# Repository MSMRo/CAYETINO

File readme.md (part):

# ⚡ Proyecto CAYETINO

Dispositivo generador de biopotenciales y señales sintéticas (EKG, EMG, EEG, RSP, PPG y ondas básicas) para entrenamiento y docencia de estudiantes de Ingeniería Biomédica.

El sistema se compone de dos módulos interconectados:
1. **Frontend / Interfaz de Control (Streamlit)**: Aplicación interactiva en Python que permite diseñar ondas básicas, sintetizar señales fisiológicas avanzadas con la librería **NeuroKit2**, inyectar fuentes de ruido clínico (interferencia electromagnética a 60 Hz, ruido térmico blanco y artefactos de movimiento), transferir los archivos vía Serial y gestionar la reproducción del hardware.
2. **Firmware de Adquisición y Emisión DAC (ESP32 en Arduino)**: Programa embebido que recibe los datos por comunicación serial por bloques con ACK, los almacena en el sistema de archivos no volátil **LittleFS**, y los reproduce en bucle continuo a través de su convertidor digital-analógico interno de 8 bits (**GPIO 25 / GPIO 26**) mediante un temporizador por hardware de 64 bits (`esp_timer`).

---

## 📁 Estructura del Repositorio

```
CAYETINO/
├── app_pyqt6/                        # Interfaz nativa de escritorio en PyQt6
│   ├── main.py                      # Punto de entrada de la aplicación de escritorio
│   ├── main_window.py               # Ventana principal e integración de pestañas
│   ├── sidebar.py                   # Enlace serial, simulación y control DAC
│   ├── tab_basic.py                 # Modo básico: formas de onda periódicas
│   ├── tab_advanced.py              # Modo avanzado: biopotenciales y NeuroKit2
│   ├── tab_manager.py               # Explorador de archivos LittleFS y reproducción DAC
│   ├── tab_guide.py                 # Guía de hardware, circuito atenuador y protocolo
│   ├── styles.py                    # Hoja de estilos moderna inspirada en Streamlit
│   ├── workers.py                   # Subprocesos QThread asíncronos para Serial
│   ├── signal_generator.py          # Motor de síntesis fisiológica y ruido
│   └── serial_comm.py               # Driver de comunicación UART y LittleFS
├── app_streamlit/                    # Interfaz web de usuario y control (Streamlit)
│   ├── app.py                       # Aplicación principal de Streamlit
│   ├── signal_generator.py          # Síntesis matemática, NeuroKit2 y ruido
│   ├── serial_comm.py               # Driver de comunicación serial y LittleFS
│   └── requirements.txt             # Dependencias en Python
├── dist/
│   └── Cayetino_ESP32/              # Carpeta de distribución del ejecutable Windows
│       └── Cayetino_ESP32.exe       # Ejecutable nativo (.exe) para PC
├── firmware_esp32/
│   └── cayetino_esp32/
│       ├── cayetino_esp32.ino       # Código Arduino/C++ para ESP32
│       └── README.md                # Guía de compilación y flasheo
├── CIRCUITO_KICAD/                  # Archivos de hardware y PCB
├── run_cayetino_exe.bat             # Lanzador directo del ejecutable .exe compilado
├── run_app_pyqt.bat                 # Lanzador de la app PyQt6 en Python
├── run_app.bat                      # Lanzador de la app Streamlit
└── README.md                        # Documentación general
```

---

## 🚀 Inicio Rápido

### 1. Ejecutar el Ejecutable .EXE (Instalable/Portable en PC)
No requiere tener Python instalado:
- Haz doble clic en **`run_cayetino_exe.bat`** o abre directamente:
  `dist\Cayetino_ESP32\Cayetino_ESP32.exe`

### 2. Ejecutar la versión PyQt6 en Python
```powershell
.\run_app_pyqt.bat
```
O directamente con Python:
```powershell
python app_pyqt6/main.py
```

### 3. Ejecución de la Interfaz Streamlit
Haz doble clic en `run_app.bat` o ejecuta:
```powershell
python -m streamlit run app_streamlit/app.py
```

---

## 🌟 Funcionalidades Detalladas

### 1. 📊 Modo Básico
- **Formas de onda disponibles**:
  - Senoidal
  - Triángulo
  - Cuadrada (con ciclo de trabajo ajustable)
  - Diente de sierra
  - Diente de sierra invertida
- **Parámetros configurables**:
  - Frecuencia de la señal ($f$ en Hz)
  - Frecuencia de muestreo ($F_s$ en Hz)
  - Duración de la ventana temporal ($T$ en segundos)
  - Amplitud y nivel de offset DC
- **Previsualización en tiempo real**: Visualización con **Plotly** de la forma de onda continua, la tensión de salida analógica ($0.0 - 3.3\text{ V}$) y el código digital cuantizado DAC ($0 - 255$).
- **Exportación**: Envío directo a la memoria flash LittleFS del ESP32 con selector de formato (`.csv`, `.txt`, `.dat`).

### 2. 🧬 Modo Avanzado (NeuroKit2 & Simulación Fisiológica)
- **Señales biomédicas sintéticas**:
  - **EKG / ECG**: Modelo dinámico de McSharry (*ecgsyn*) o modelo estándar, con ritmo cardíaco ajustable (BPM).
  - **EMG**: Electromiografía con ráfagas de activación y duración de contracción configurables.
  - **EEG**: Ondas electroencefalográficas con mezcla de ritmos fisiológicos (Alpha, Beta, Theta y componente estocástico 1/f).
  - **RSP**: Dinámica respiratoria sinusoidal con variabilidad.
  - **PPG**: Pulso arterial y fotopletismografía.
- **Módulo de Contaminación de Señales (Inyección de Ruido)**:
  - ⚡ **Interferencia de Red Eléctrica**: Onda senoidal armónica (60 Hz por defecto en Perú/América o 50 Hz) con amplitud graduable.
  - 🌫️ **Ruido Blanco Térmico**: Distribución Gaussiana $\mathcal{N}(0, \sigma^2)$ para modelar ruido de electrodo y circuitería analógica.
  - 📍 **Ruido Impulsional**: Artefactos de movimiento y desacople de electrodos (spikes aleatorios bipolares).
- **Análisis en Frecuencia (FFT)**: Espectro de potencia en tiempo real para verificar la presencia de armónicos contaminantes (pico a 60 Hz).

### 3. 💾 Gestor de Archivos en LittleFS y Control del DAC
- **Explorador Flash**: Muestra un cuadro/tarjeta con todos los archivos guardados en la memoria del ESP32, indicando:
  - Nombre del archivo
  - Frecuencia de muestreo original ($F_s$)
  - Cantidad total de muestras
  - Duración de la ventana en segundos
  - Tamaño ocupado en memoria Flash
- **Controles de Reproducción**:
  - ▶ **Reproducir (PLAY)**: El ESP32 carga la señal en memoria RAM y comienza la emisión analógica ininterrumpida en bucle por su DAC.
  - ⏹ **Detener (STOP)**: Detiene la emisión analógica y coloca la salida en nivel seguro de reposo ($\sim 1.65\text{ V}$).
  - 🗑 **Eliminar**: Borra el archivo seleccionado del sistema de archivos LittleFS.
  - 🔄 **Actualizar**: Lee el estado actual y archivos de la memoria del ESP32.
---

## 🏛️ Arquitectura del Sistema y Diagramas Técnicos (Mermaid)

Para comprender en profundidad el funcionamiento integral de la plataforma Cayetino (desde el diseño en el frontend de escritorio hasta la síntesis en tiempo real por interrupción en el microcontrolador), se detallan a continuación los diagramas arquitectónicos del proyecto:

---

### 1. 📐 Modelo C4 de Arquitectura

El modelo C4 permite descomponer la arquitectura en diferentes niveles de abstracción jerárquica:

#### Nivel 1: Diagrama de Contexto del Sistema (System Context)
Muestra cómo interactúa el usuario (estudiante o investigador biomédico) con la plataforma Cayetino y los equipos de instrumentación clínica externos.

```mermaid
flowchart TB
  subgraph Contexto ["C4 - Nivel 1: Contexto del Sistema CAYETINO"]
    User["👨‍🔬 Usuario Biomédico<br>[Estudiante / Investigador / Docente]<br>Diseña ondas, inyecta ruido clínico y controla reproducción"]
    
    CayetinoSystem["⚡ <b>Sistema CAYETINO</b><br>[Generador de Biopotenciales y Ondas Sintéticas]<br>Plataforma de software y hardware embebido basada en ESP32"]
    
    BioAmp["🩺 Amplificador de Biopotenciales<br>[AD620 / INA128 / ADS1299]<br>Captación de señales en rango de microvoltios/milivoltios"]
    
    Oscilloscope["📈 Instrumental de Diagnóstico<br>[Osciloscopio / DAQ / Raspberry Pi Pico ADC]<br>Medición y análisis directo en dominio temporal y espectral"]
    
    PC_Host["💻 Computadora Personal Windows<br>[Host PC]<br>Alimentación USB y canal UART bidireccional (115200 bps)"]

    User -->|"Configura parámetros y gestiona memoria Flash"| CayetinoSystem
    CayetinoSystem -->|"Emite señal atenuada segura (0.1 a 3.3 mV)"| BioAmp
    CayetinoSystem -->|"Emite señal DAC pura (0.0 a 3.3 V)"| Oscilloscope
    PC_Host <-->|"Enlace USB-UART Serial (CP210x)"| CayetinoSystem
  end
```

#### Nivel 2: Diagrama de Contenedores (Containers)
Describe las aplicaciones ejecutables, el firmware embebido en el ESP32, el almacenamiento Flash y el circuito atenuador pasivo.

```mermaid
flowchart TB
  subgraph Containers ["C4 - Nivel 2: Diagrama de Contenedores"]
    User["👨‍🔬 Usuario Biomédico"]

    subgraph HostPC ["Computadora Personal (Entorno Windows)"]
      PyQtApp["🖥️ <b>Aplicación de Escritorio PyQt6</b><br>[Python 3.12 / PyQt6 / PyInstaller .EXE]<br>Interfaz gráfica nativa de alto rendimiento con pyqtgraph y workers QThread"]
      StreamlitApp["🌐 <b>Aplicación Web Streamlit</b><br>[Python / Streamlit / Plotly]<br>Panel web interactivo accesible vía navegador local"]
    end

    subgraph EmbeddedESP32 ["Módulo Embebido ESP32 (Hardware Microcontrolador)"]
      FirmwareCore["⚙️ <b>Firmware C++ Cayetino</b><br>[Arduino Core / FreeRTOS / UART Driver]<br>Intérprete de comandos seriales, parser de chunks y despachador"]
      TimerEngine["⏱️ <b>Temporizador de Hardware</b><br>[esp_timer 64-bit]<br>Genera interrupciones periódicas a frecuencia exacta Fs"]
      FlashStorage[("💾 <b>Sistema de Archivos Flash</b><br>[LittleFS non-volatile]<br>Almacena archivos .csv, .txt y .dat de señales")]
      DACModule["⚡ <b>Convertidor DAC 8-bit</b><br>[Hardware DAC interno ESP32]<br>Emisión analógica por GPIO 25 o GPIO 26"]
    end

    subgraph CircuitPCB ["Placa de Acondicionamiento (Circuito KiCad)"]
      Attenuator["🎛️ <b>Divisor Atenuador Pasivo 1000:1</b><br>[R1 = 10 kΩ, R2 = 10 Ω]<br>Reduce la tensión de 3.3 V a niveles fisiológicos seguros"]
    end

    BioAmpExternal["🩺 Amplificador / Electrocardiógrafo Externo"]

    User -->|"Control interactivo nativo"| PyQtApp
    User -->|"Control web"| StreamlitApp
    PyQtApp <-->|"Comandos de texto y datos UART (115200 bps)"| FirmwareCore
    StreamlitApp <-->|"Comandos de texto y datos UART (115200 bps)"| FirmwareCore

    FirmwareCore <-->|"Lectura y escritura por bloques"| FlashStorage
    FirmwareCore -->|"Carga buffer a RAM y configura periodo"| TimerEngine
    TimerEngine -->|"Interrupción periódica dacWrite()"| DACModule
    DACModule -->|"Tensión analógica (0.0 V - 3.3 V)"| Attenuator
    Attenuator -->|"Tensión biomédica (0.1 mV - 3.3 mV)"| BioAmpExternal
  end
```

#### Nivel 3: Diagrama de Componentes (Components)
Detalla los módulos internos del frontend PyQt6 y las rutinas del firmware Arduino/C++.

```mermaid
flowchart TB
  subgraph ComponentsDiagram ["C4 - Nivel 3: Componentes de Software y Firmware"]
    subgraph FrontendPyQt6 ["Contenedor: Aplicación de Escritorio (app_pyqt6)"]
      MainWindow["<b>MainWindow</b><br>Ventana principal, control de pestañas y notificaciones flotantes"]
      Sidebar["<b>SidebarWidget</b><br>Gestión de puertos COM, modo simulación, selección DAC y formateo"]
      TabBasic["<b>TabBasicWave</b><br>Generador de ondas sintéticas, previsualización dual y guardado"]
      TabAdv["<b>TabAdvancedBio</b><br>Modelado NeuroKit2, inyector de 3 ruidos clínicos y FFT"]
      TabMgr["<b>TabManager</b><br>Tabla LittleFS, reproductor PLAY/STOP y prueba senoidal 5Hz"]
      TabGde["<b>TabGuide</b><br>Documentación interactiva y tabla del protocolo serial"]
      SignalGen["<b>signal_generator.py</b><br>Motor numérico: scipy.signal, neurokit2 y cuantización 8-bit"]
      Workers["<b>workers.py (QThreads)</b><br>ConnectWorker, SaveSignalWorker, PlayWorker, ListWorker, etc."]
      SerialDriver["<b>serial_comm.py (CayetinoSerial)</b><br>Controlador de comunicación física pyserial y virtual"]
    end

    subgraph FirmwareESP32 ["Contenedor: Firmware ESP32 (cayetino_esp32.ino)"]
      CmdParser["<b>Command Parser</b><br>Lectura de líneas UART, extracción de comandos y argumentos"]
      FsManager["<b>LittleFS File Manager</b><br>Lectura de encabezados, escritura incremental y borrado"]
      DacController["<b>Playback Controller</b><br>Carga de muestras a RAM estática y gestión de estados"]
      TimerService["<b>esp_timer Service</b><br>Configuración de alarma de microsegundos"]
      DacOutput["<b>DAC Hardware Output</b><br>Escritura analógica directa en registro DAC"]
    end

    MainWindow --> Sidebar
    MainWindow --> TabBasic
    MainWindow --> TabAdv
    MainWindow --> TabMgr
    MainWindow --> TabGde

    TabBasic --> SignalGen
    TabAdv --> SignalGen

    Sidebar --> Workers
    TabBasic --> Workers
    TabAdv --> Workers
    TabMgr --> Workers

    Workers --> SerialDriver
    SerialDriver <-->|"Línea Serial UART (TX/RX)"| CmdParser

    CmdParser --> FsManager
    CmdParser --> DacController
    DacController --> FsManager
    DacController --> TimerService
    TimerService --> DacOutput
  end
```

---

### 2. 🔄 Diagrama de Secuencia (Protocolo UART y Control de Flujo)

Describe el ciclo de vida completo de la comunicación entre la aplicación en la PC y el microcontrolador: handshake, guardado con confirmación por bloques (*stop-and-wait ACK*), reproducción continua por hardware y detención segura.

```mermaid
sequenceDiagram
  autonumber
  actor User as Usuario Biomédico
  participant UI as Interfaz Gráfica (PyQt6)
  participant Worker as QThread Worker (Background)
  participant Driver as CayetinoSerial (Driver PC)
  participant SerialPort as Puerto Serial COM (USB UART)
  participant ESP32 as Firmware ESP32 (Parser)
  participant LittleFS as Memoria Flash (LittleFS)
  participant Timer as esp_timer (Hardware Timer)
  participant DAC as DAC 8-bit (GPIO 25/26)
  participant Circuit as Divisor Atenuador (1000:1)

  %% 1. Handshake
  Note over User, ESP32: 1. Establecimiento de Enlace Serial (Handshake)
  User->>UI: Clic en "Conectar" (COM7, 115200 bps)
  UI->>Worker: Iniciar ConnectWorker(port, 115200)
  Worker->>Driver: connect(port, baudrate)
  Driver->>SerialPort: Abrir conexión COM y limpiar buffers
  Driver->>SerialPort: Enviar "PING\n"
  SerialPort->>ESP32: Recibe "PING"
  ESP32-->>SerialPort: Responde "PONG:CAYETINO_ESP32_OK\n"
  SerialPort-->>Driver: Lectura de respuesta PONG
  Driver-->>Worker: Conexión verificada exitosa (True)
  Worker-->>UI: Emite finished(True)
  UI-->>User: Actualiza estado a "🟢 Conectado"

  %% 2. Guardado con control de flujo
  Note over User, LittleFS: 2. Transmisión y Grabación de Señal en Flash con Flow-Control
  User->>UI: Diseña EKG y pulsa "🚀 Enviar y Guardar"
  UI->>Worker: Iniciar SaveSignalWorker("ekg_5s.csv", 250 Hz, 1250 muestras)
  Worker->>Driver: save_file(filename, fs, dac_values, chunk_size=64)
  Driver->>SerialPort: Enviar "SAVE_START:ekg_5s.csv:250:1250\n"
  SerialPort->>ESP32: Recibe SAVE_START
  ESP32->>LittleFS: LittleFS.open("ekg_5s.csv", "w")
  ESP32-->>SerialPort: Responde "READY_CHUNKS\n"
  SerialPort-->>Driver: Confirma preparación del microcontrolador

  loop Transmisión por bloques de 64 muestras con verificación ACK
    Driver->>SerialPort: Enviar "CHUNK:128,135,142,...\n"
    SerialPort->>ESP32: Escribe bloque en archivo de Flash
    ESP32-->>SerialPort: Responde "ACK_CHUNK\n"
    SerialPort-->>Driver: ACK_CHUNK recibido
    Driver-->>Worker: Notifica avance de progreso (p %)
    Worker-->>UI: Actualiza QProgressBar en tiempo real
  end

  Driver->>SerialPort: Enviar "SAVE_END\n"
  ESP32->>LittleFS: file.close() (Consolida archivo)
  ESP32-->>SerialPort: Responde "OK_SAVE:ekg_5s.csv:1250\n"
  Driver-->>Worker: Guardado finalizado con éxito
  Worker-->>UI: Despliega notificación toast "✅ Archivo grabado"
  UI->>Worker: Iniciar ListFilesWorker() para refrescar tabla

  %% 3. Reproducción continua por DAC
  Note over User, Circuit: 3. Carga en RAM y Reproducción Analógica Continua
  User->>UI: Selecciona "ekg_5s.csv" y pulsa "▶️ REPRODUCIR (PLAY)"
  UI->>Worker: Iniciar PlayFileWorker("ekg_5s.csv")
  Worker->>Driver: play_file("ekg_5s.csv")
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
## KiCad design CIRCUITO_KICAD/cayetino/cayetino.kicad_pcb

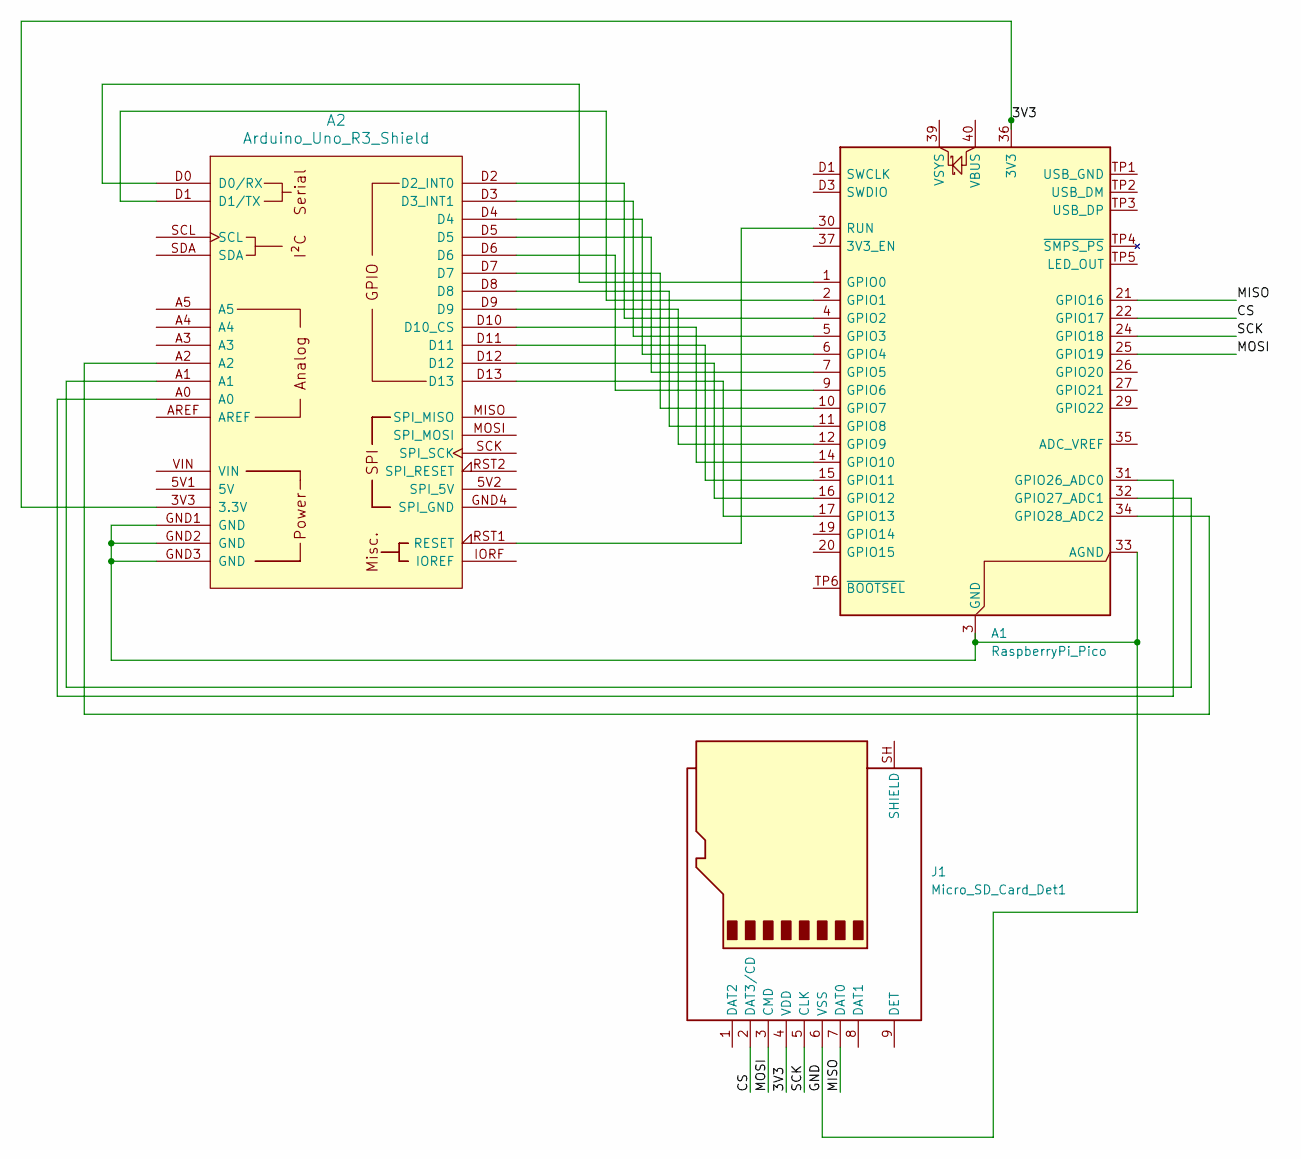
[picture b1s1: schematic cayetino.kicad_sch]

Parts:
A1: RaspberryPi_Pico; RaspberryPi_Pico_SMD_only_pins
A2: Arduino_Uno_R3_Shield; Arduino_Uno_R3_only_headers
J1: Micro_SD_Card_Det1; J_SD_Card-micro_socket_A

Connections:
/3V3: A1.36 (3V3), A2.3V3 (3.3V), J1.4 (VDD)
/CS: A1.22 (GPIO17), J1.2 (DAT3/CD)
/GND: A1.3 (GND), A1.8 (GND), A1.13 (GND), A1.18 (GND), A1.23 (GND), A1.28 (GND), A1.33 (AGND), A1.38 (GND), A1.D2 (GND), A2.GND1 (GND), A2.GND2 (GND), A2.GND3 (GND), J1.6 (VSS)
/MISO: A1.21 (GPIO16), J1.7 (DAT0)
/MOSI: A1.25 (GPIO19), J1.3 (CMD)
/SCK: A1.24 (GPIO18), J1.5 (CLK)
unnamed: A1.1 (GPIO0), A2.D0 (D0/RX)
unnamed: A1.2 (GPIO1), A2.D1 (D1/TX)
unnamed: A1.4 (GPIO2), A2.D2 (D2_INT0)
unnamed: A1.5 (GPIO3), A2.D3 (D3_INT1)
unnamed: A1.6 (GPIO4), A2.D4
unnamed: A1.7 (GPIO5), A2.D5
unnamed: A1.9 (GPIO6), A2.D6
unnamed: A1.10 (GPIO7), A2.D7
unnamed: A1.11 (GPIO8), A2.D8
unnamed: A1.12 (GPIO9), A2.D9
unnamed: A1.14 (GPIO10), A2.D10 (D10_CS)
unnamed: A1.15 (GPIO11), A2.D11
unnamed: A1.16 (GPIO12), A2.D12
unnamed: A1.17 (GPIO13), A2.D13
unnamed: A1.31 (GPIO26_ADC0), A2.A0
unnamed: A1.32 (GPIO27_ADC1), A2.A1
unnamed: A1.34 (GPIO28_ADC2), A2.A2
unnamed: A1.30 (RUN), A2.RST1 (RESET)

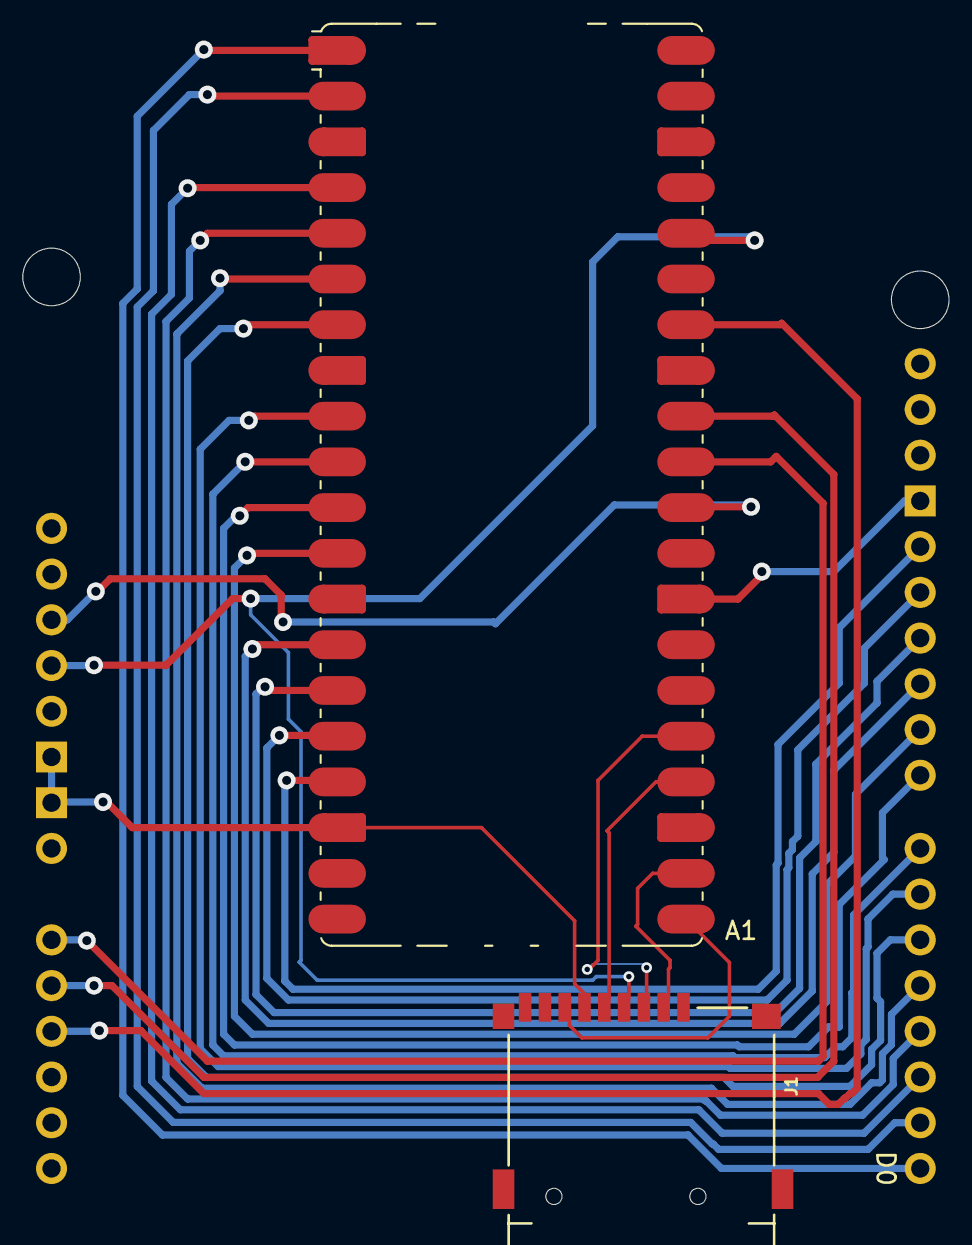
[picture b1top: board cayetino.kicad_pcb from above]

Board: 2 copper layers, 3 parts (0 on the bottom side), 24 nets.
